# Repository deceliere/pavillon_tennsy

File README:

a simple MP3 player - for a sound installation 

 + Teensy 4.0 
 + adafruit VS1053 
 + TPA2016 amp
 + waveshare 1.3inch OLED Module 64 × 128 soft SPI
 + mosfet driving lamp following Vu meter level

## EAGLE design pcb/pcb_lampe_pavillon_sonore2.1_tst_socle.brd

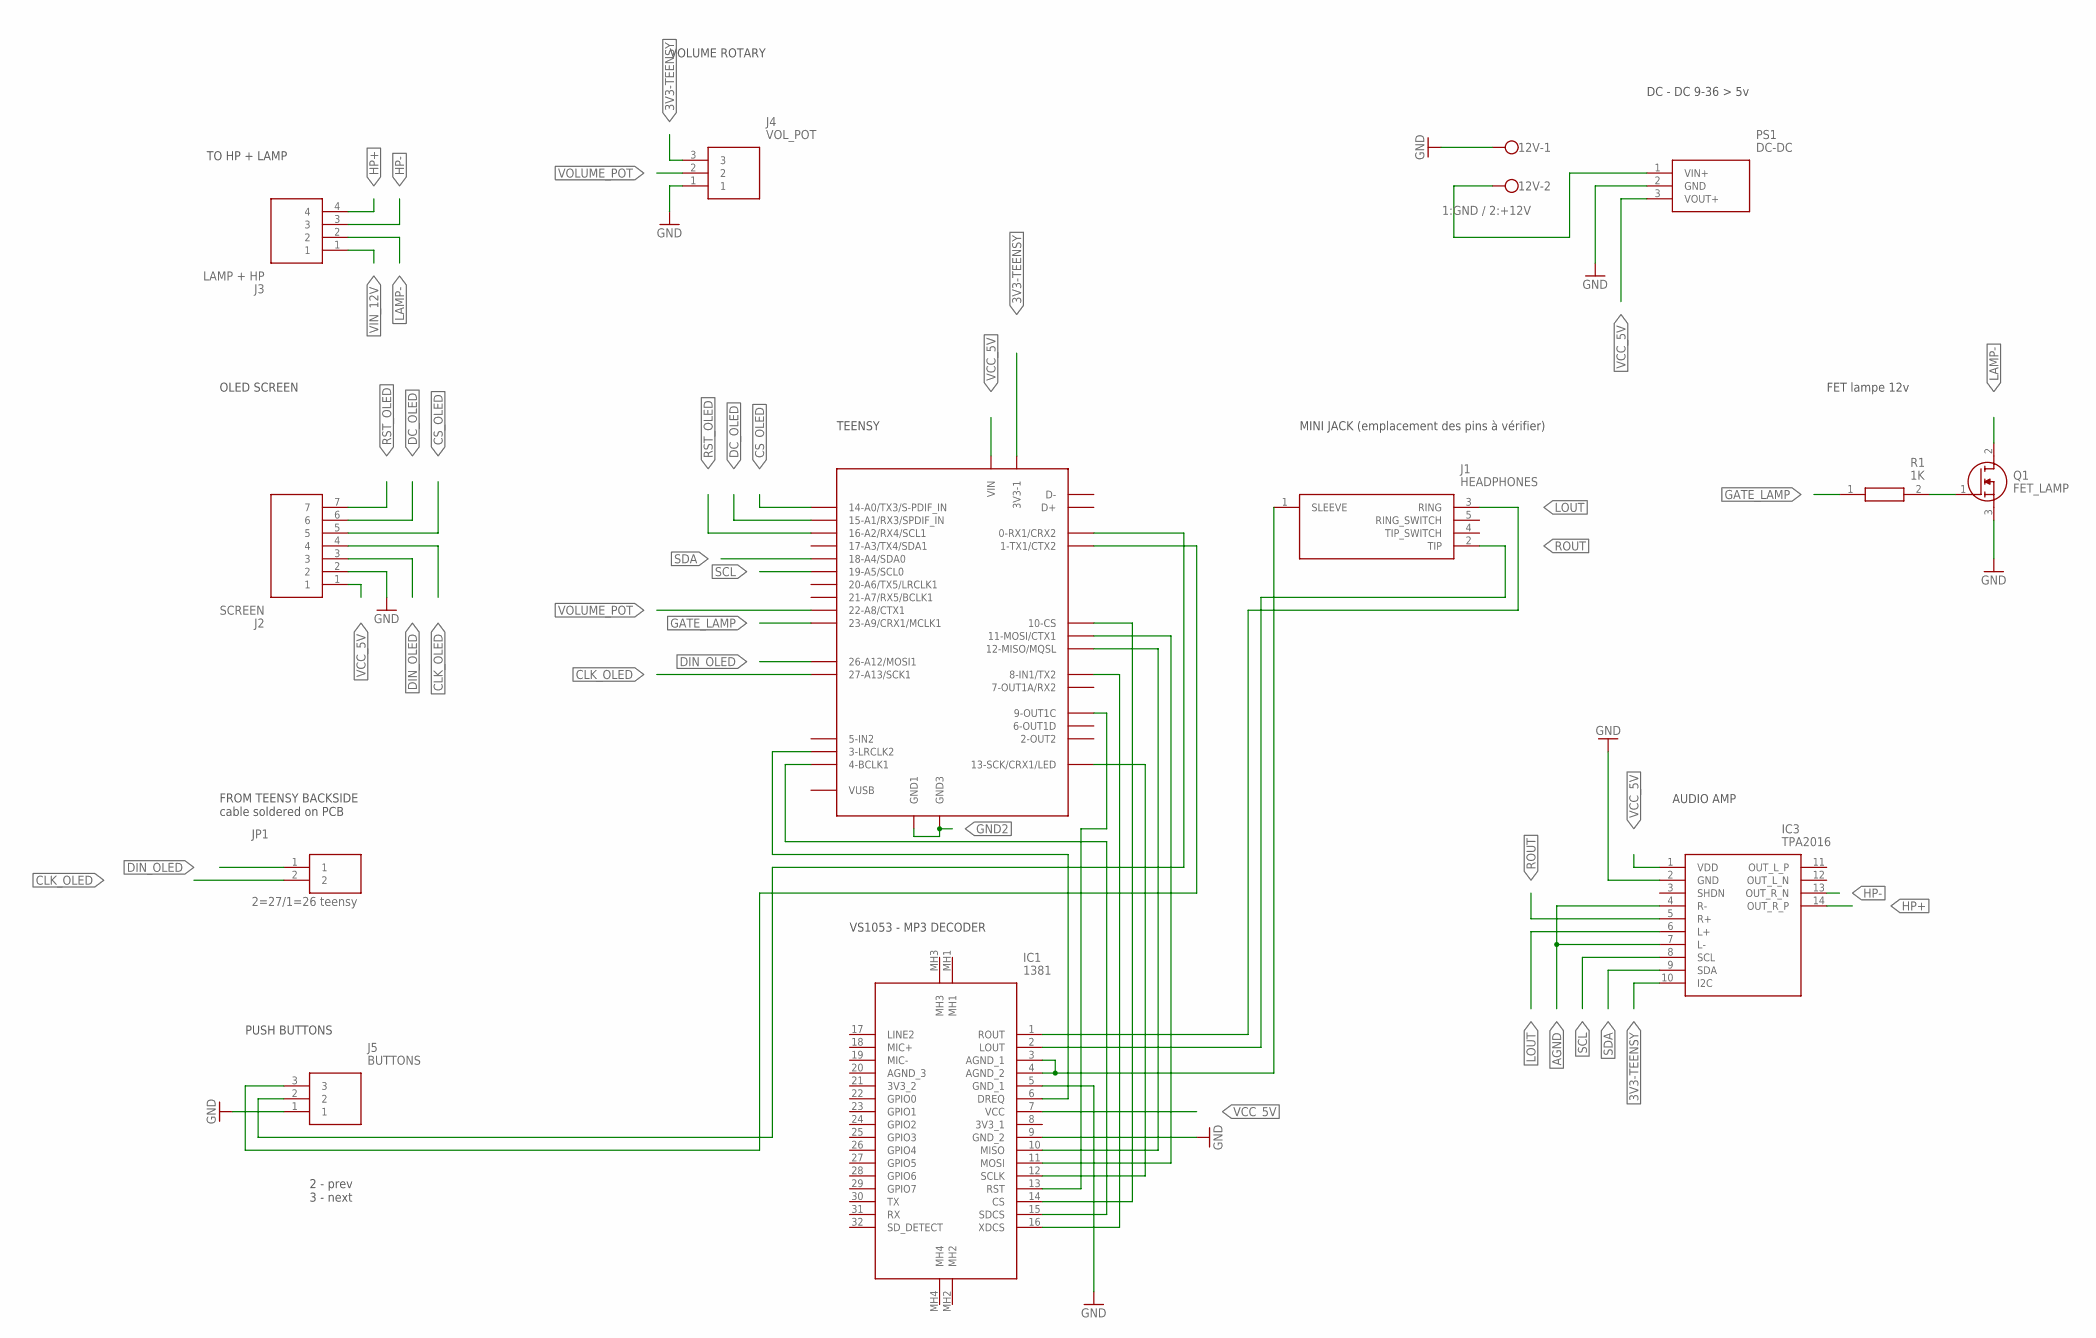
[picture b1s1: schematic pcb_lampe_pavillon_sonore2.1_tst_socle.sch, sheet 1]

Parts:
12V: 1:GND / 2:+12V; W237-102
IC1: 1381
IC3: TPA2016
J1: HEADPHONES; SJ13525NGGR
J2: SCREEN; SHDR7W50P0X200_1X7_1590X450X60_RA
J3: LAMP + HP; SHDR4W50P0X200_1X4_990X450X600_RA
J4: VOL_POT; S3B-PH-K-S
J5: BUTTONS; S3B-PH-K-S
JP1: 2=27/1=26 teensy; SHDRRA2W50P0X200_1X2_590X760X4
PS1: DC-DC; TSR-1-24120
Q1: FET_LAMP; TO254P465X1024X2050-3P
R1: 1K; RESAD1650W60L650D250
U$1: TEENSY40

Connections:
3V3-TEENSY: IC3.10 (I2C), J4.3, U$1.3V3-1
AGND: IC1.3 (AGND_1), IC1.4 (AGND_2), IC3.4 (R-), IC3.7 (L-), J1.1 (SLEEVE)
CLK_OLED: J2.4, JP1.2, U$1.27-A13/SCK1
CS_OLED: J2.5, U$1.14-A0/TX3/S-PFI_OUT (14-A0/TX3/S-PDIF_IN)
DC_OLED: J2.6, U$1.15-A1/RX3/S-PDIF_IN (15-A1/RX3/SPDIF_IN)
DIN_OLED: J2.3, JP1.1, U$1.26-A12/MOSI1
GATE_LAMP: R1.1, U$1.23-A9/CRX1/CCLK1 (23-A9/CRX1/MCLK1)
GND2: 12V.1, IC1.5 (GND_1), IC1.9 (GND_2), IC3.2 (GND), J2.2, J4.1, J5.1, PS1.2 (GND), Q1.3 (S), U$1.GND1, U$1.GND3; also elsewhere on the board
HP+: IC3.14 (OUT_R_P), J3.4
HP-: IC3.13 (OUT_R_N), J3.3
LAMP-: J3.2, Q1.2 (D)
LOUT: IC1.1 (ROUT), IC3.6 (L+), J1.3 (RING)
unnamed: IC1.12 (SCLK), U$1.13-SCK/CRX1/LED
unnamed: IC1.10 (MISO), U$1.12-MIO/MQSL (12-MISO/MQSL)
unnamed: IC1.11 (MOSI), U$1.11-MOSI/CTX1
unnamed: IC1.14 (CS), U$1.10-CS/MQSR (10-CS)
unnamed: IC1.16 (XDCS), U$1.8-TX2/IN1 (8-IN1/TX2)
unnamed: IC1.15 (SDCS), U$1.4-BCLK2 (4-BCLK1)
unnamed: IC1.13 (RST), U$1.9-OUT1C
unnamed: J5.2, U$1.0-RX1 (0-RX1/CRX2)
unnamed: J5.3, U$1.1-TX1 (1-TX1/CTX2)
unnamed: IC1.6 (DREQ), U$1.3-LRCLK2
unnamed: Q1.1 (G), R1.2
ROUT: IC1.2 (LOUT), IC3.5 (R+), J1.2 (TIP)
RST_OLED: J2.7, U$1.16-A2/RX4/SCL1
SCL: IC3.8 (SCL), U$1.19-A5/SCL0
SDA: IC3.9 (SDA), U$1.18-A4/SDA0
VCC_5V: IC1.7 (VCC), IC3.1 (VDD), J2.1, PS1.3 (VOUT+), U$1.VIN
VIN_12V: 12V.2, J3.1, PS1.1 (VIN+)
VOLUME_POT: J4.2, U$1.22-A8/CTX1

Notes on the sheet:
MINI JACK (emplacement des pins à vérifier)
AUDIO AMP
VS1053 - MP3 DECODER
TEENSY
FROM TEENSY BACKSIDE cable soldered on PCB
OLED SCREEN
PUSH BUTTONS
DC - DC 9-36 > 5v
FET lampe 12v
TO HP + LAMP
VOLUME ROTARY
2 - prev 3 - next

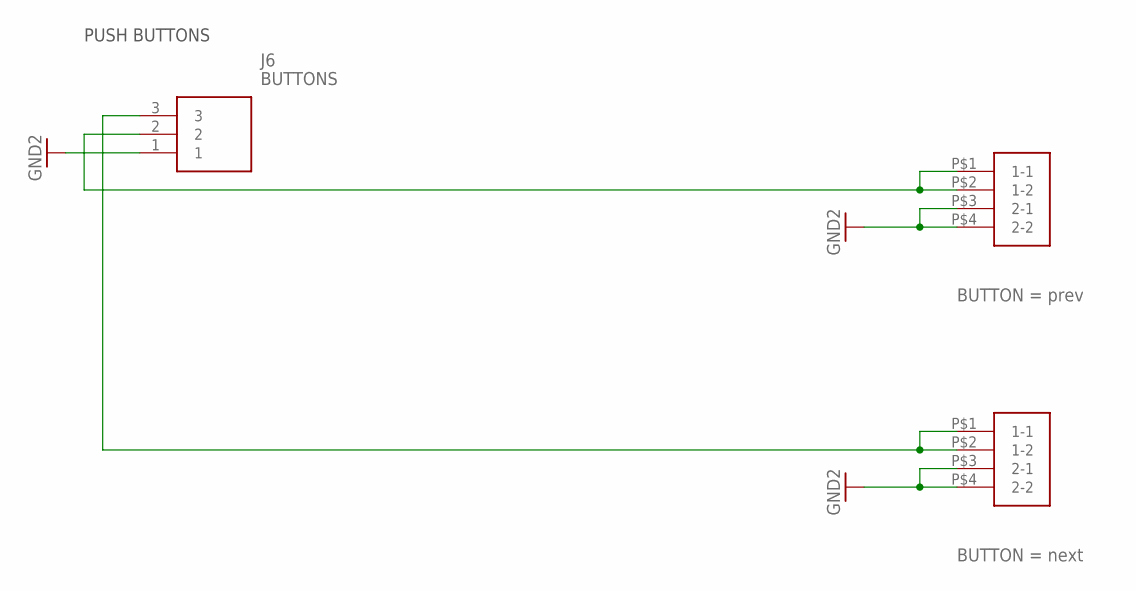
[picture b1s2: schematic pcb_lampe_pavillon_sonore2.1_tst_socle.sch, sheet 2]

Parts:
J6: BUTTONS; S3B-PH-K-S
U$2, U$3: SWITCH12X12

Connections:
GND2: J6.1, U$2.P$3 (2-1), U$2.P$4 (2-2), U$3.P$3 (2-1), U$3.P$4 (2-2); also elsewhere on the board
unnamed: J6.2, U$2.P$1 (1-1), U$2.P$2 (1-2)
unnamed: J6.3, U$3.P$1 (1-1), U$3.P$2 (1-2)

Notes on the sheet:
PUSH BUTTONS

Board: 2 copper layers, 16 parts (0 on the bottom side), 32 nets, no tracks yet.

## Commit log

2023-06-28 inital commit - working player + screen + fet + amp, but no navigation
2023-06-29 VU meter ok, PWM on pin 23 - id3 ok on oled SCREEN FLICKER
2023-06-29 id3 sur oled working. plus de flicker oled semble-t-il TBC
2023-07-01 listing and sorting directoy .mp3 only - id3 quite working TBC
2023-07-01 first loop test ok - n/a and filename displayed if no id3 readable
2023-07-01 issue while reboot standalone
2023-07-02 finally got this working on reboot - gosh
2023-07-02 previous button quite working, stil a lot to do
2023-07-03 add tracknumber + total number on display
2023-07-04 add stopPlaying for every pushbutton (temporary remove currentTrack / totalfile display)
2023-07-04 added currentTrack / totalfile diplay. to be checked on long playback
2023-07-04 add flush at stopPlaying (TBC on long play)
2023-07-04 add resetPosition at every stop / next / previous and track change
2023-07-05 add time as min:sec
2023-07-05 add DEBUG define + macro
2023-09-27 ajout du PCB v1.0
2023-10-05 add test id3v2 reader + manage utf-8 sepcial char
2023-10-09 before add id3v2
2023-10-09 add pcb
2023-10-15 pcb v1.0 prod
2023-10-15 wip working
2023-10-15 platformio config
2023-10-15 io config teensy 41
2023-10-15 working from teensy headless
    - moved vs1053 patch to specific header file
    - solved lumonoisty issue on oled 1.3 - changed contrast in sh1107 specific header file
    - working on scrolling text
    - working on UTF-8 compatibility (solved but to be checked)
    - working on file list order begining with number
2023-10-15 working from teensy headless
    - moved vs1053 patch to specific header file
    - solved luminosity issue on oled 1.3 - changed contrast in sh1107 specific header file
    - working on scrolling text
    - working on UTF-8 compatibility (solved but to be checked)
    - working on file list order begining with numbers
2023-10-15 text scroll WIP
    - simple text scrolling on two lines
    - scolling only if text is bigger than total pixel width
    - UTF8 ok
2023-10-16 forget taglib -dev own tagreader
2023-10-16 change text display -> UTF8, custom id3v2 WIP
2023-10-16 remove copyFile (not working)
2023-10-16 change old file cpp name
2023-10-17 add simple id3v2 parser + strTuUpper (capitalize track title)
2023-10-19 id3v2 ok + filenames issue ok
2023-10-19 changed oled millis to elapsed
2023-10-19 scolling ok - display filename if no id3v2 + n/a if no info
2023-10-22 pcb insert socle shaped
2023-10-22 add logo at startup
2023-10-22 remove taglib lib refs
2023-10-22 add random at startup
2023-10-23 re-enable vumeter + add LOGO STUCK macro
2023-10-24 wip exponential lamp FET level
2023-10-24 add ramp + exponential (test ft - WIP)
2023-10-26 - LAMP fet + volume Exponential OK - volume SQRT (natural volume)
2023-10-26 minor changes + corr + clean
2023-10-27 added play current track (instead of previous track) in 1 sec push prevButton
2023-10-27 add pause with logo 3sec between tracks + minor corrections
2023-10-27 change macro DEBUG to DEBUG_PAVILLON
2023-11-01 id3v2 versions support WIP + unicode display fix + id3v2 wip support for v2.0 + convert decimal unicode to multiple byte/char (for display on oled)
2023-11-01 minor corr and syntax fixes
2023-11-01 pcb v2.0 update to custom shape
2023-11-01 add README basic
2023-11-01 move_readme
2023-11-01 update_readme
2023-11-08 pcb v2.1
2023-11-08 error commit - hope i didn't break anything
2023-11-13 change NEXT button input
2023-11-14 add syncsafe size decoder + modif size for text display to 1024
2023-11-19 ft for remplacing u{2019} apostrophe with standrad '39 apostrophe
2023-11-19 pcb + base drawings (alors WOOD) modif
2023-11-27 pcb and design updates ANDREA + headphone holder v2
2024-04-06 version 2.0 -add version + date
2024-06-11 add oled offests
2024-09-19 + add manual git hash in macro - remove unused tagreader ft + add "no valid file" check & message
2024-09-19 + add python script to get git hash + current date
2024-09-19 variouls tests updates (ID3 and others)
2024-09-19 add latest PCB and model updates
2024-09-19 main header minor update
2024-09-19 add TODO file
2024-09-19 update TODO
2024-09-19 + add tech sheet on git + add base drawing andra v16 + add logos
2024-09-19 - remove tech sheet from git
2024-09-20 moved out all vs1053 headers to vs1053B.h
2024-09-20 + created variables.h + set variables as extern + created vs1053b.ccp + big clean in play.ccp (master script)
2024-09-20 + updated version to 2.4 + hash + modified file name TODO
